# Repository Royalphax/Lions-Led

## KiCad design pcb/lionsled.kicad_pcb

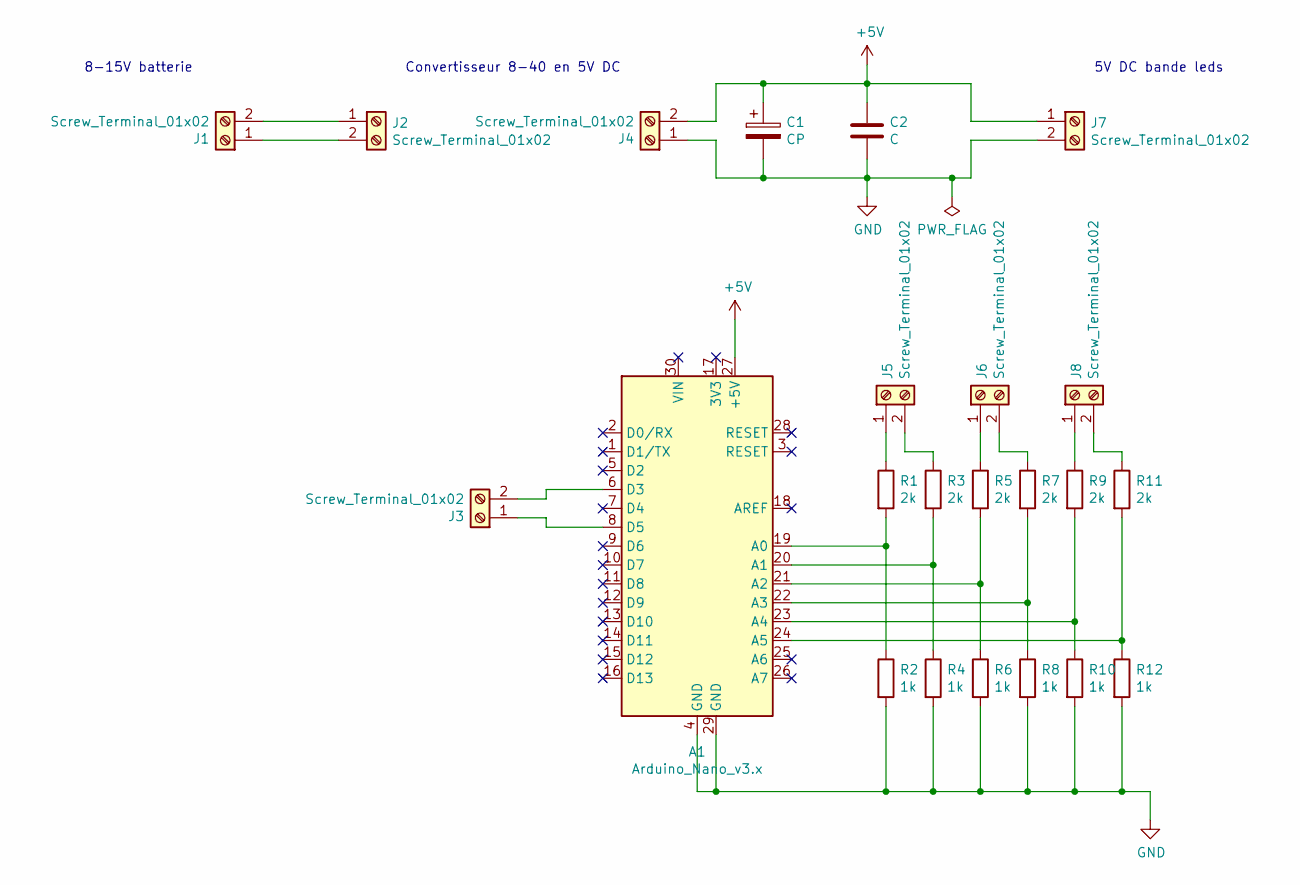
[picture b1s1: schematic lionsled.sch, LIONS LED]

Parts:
A1: Arduino_Nano_v3.x; Arduino_Nano_WithMountingHoles
C1: CP; C_pol
C2: C
J1, J2, J3, J4, J5, J6, J7, J8: Screw_Terminal_01x02; PCB_Terminal
R1, R3, R5, R7, R9, R11: 2k; R
R2, R4, R6, R8, R10, R12: 1k; R

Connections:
+5V: A1.27 (+5V), C1.1, C2.1, J4.2, J7.1
GND: A1.4 (GND), A1.29 (GND), C1.2, C2.2, J4.1, J7.2, R2.2, R4.2, R6.2, R8.2, R10.2, R12.2
unnamed: A1.6 (D3), J3.2
unnamed: A1.8 (D5), J3.1
unnamed: A1.19 (A0), R1.2, R2.1
unnamed: A1.20 (A1), R3.2, R4.1
unnamed: A1.21 (A2), R5.2, R6.1
unnamed: A1.22 (A3), R7.2, R8.1
unnamed: A1.23 (A4), R9.2, R10.1
unnamed: A1.24 (A5), R11.2, R12.1
unnamed: J1.1, J2.2
unnamed: J1.2, J2.1
unnamed: J5.1, R1.1
unnamed: J5.2, R3.1
unnamed: J6.1, R5.1
unnamed: J6.2, R7.1
unnamed: J8.1, R9.1
unnamed: J8.2, R11.1

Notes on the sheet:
Convertisseur 8-40 en 5V DC
8-15V batterie
5V DC bande leds

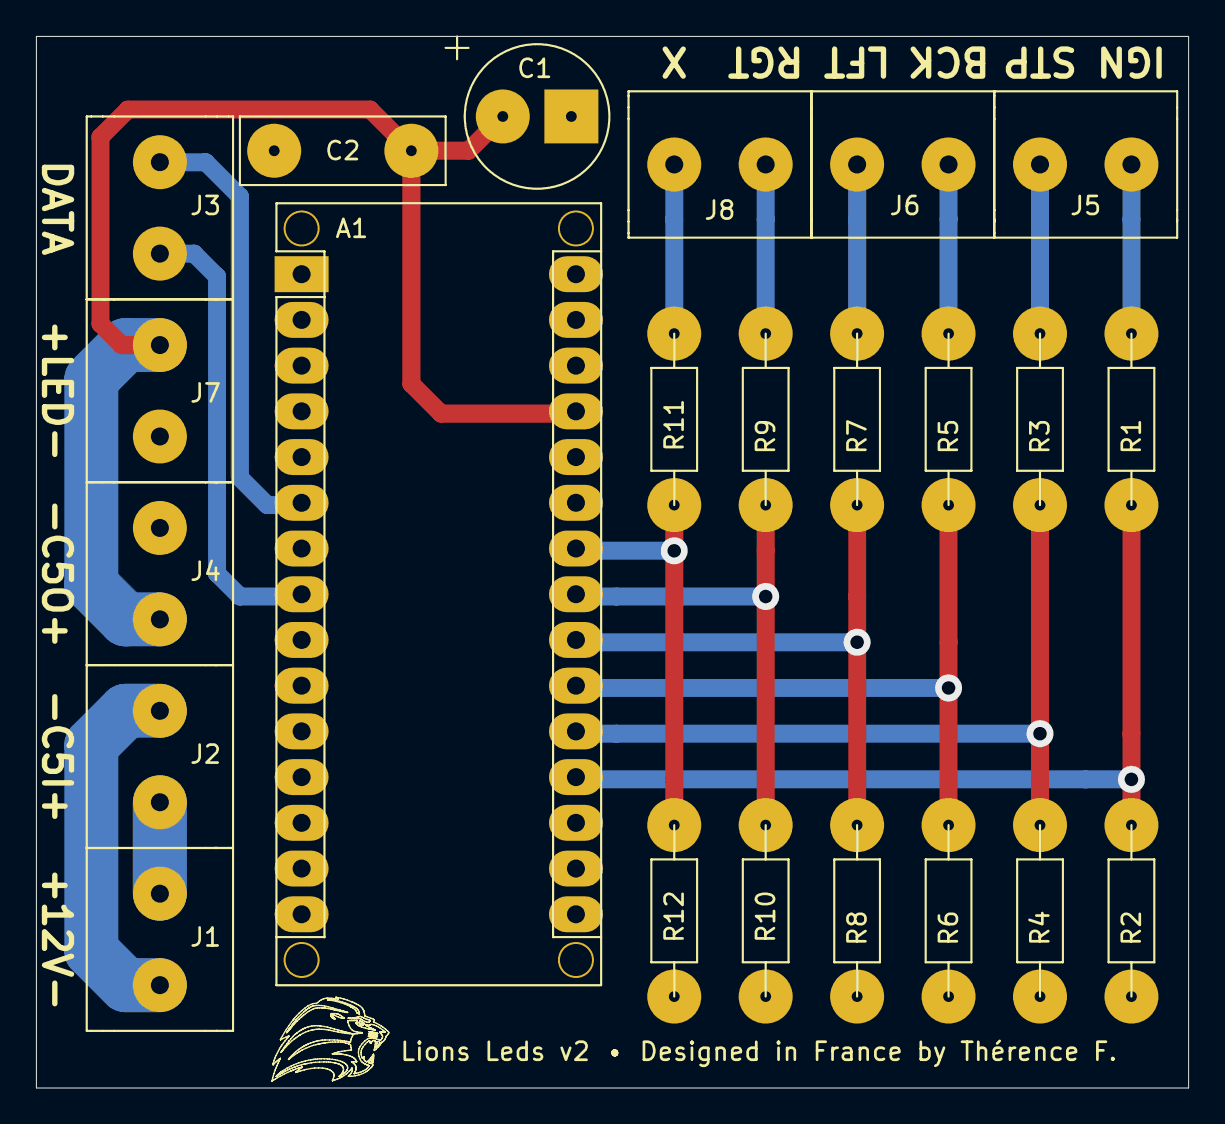
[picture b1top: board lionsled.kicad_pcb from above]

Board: 2 copper layers, 64.0 x 58.4 mm, 23 parts (0 on the bottom side), 18 nets.

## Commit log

2021-11-08 Init commit
